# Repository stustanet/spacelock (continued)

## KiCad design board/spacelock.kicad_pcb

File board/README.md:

# Board design

Printed circuit board with all the electrical components.

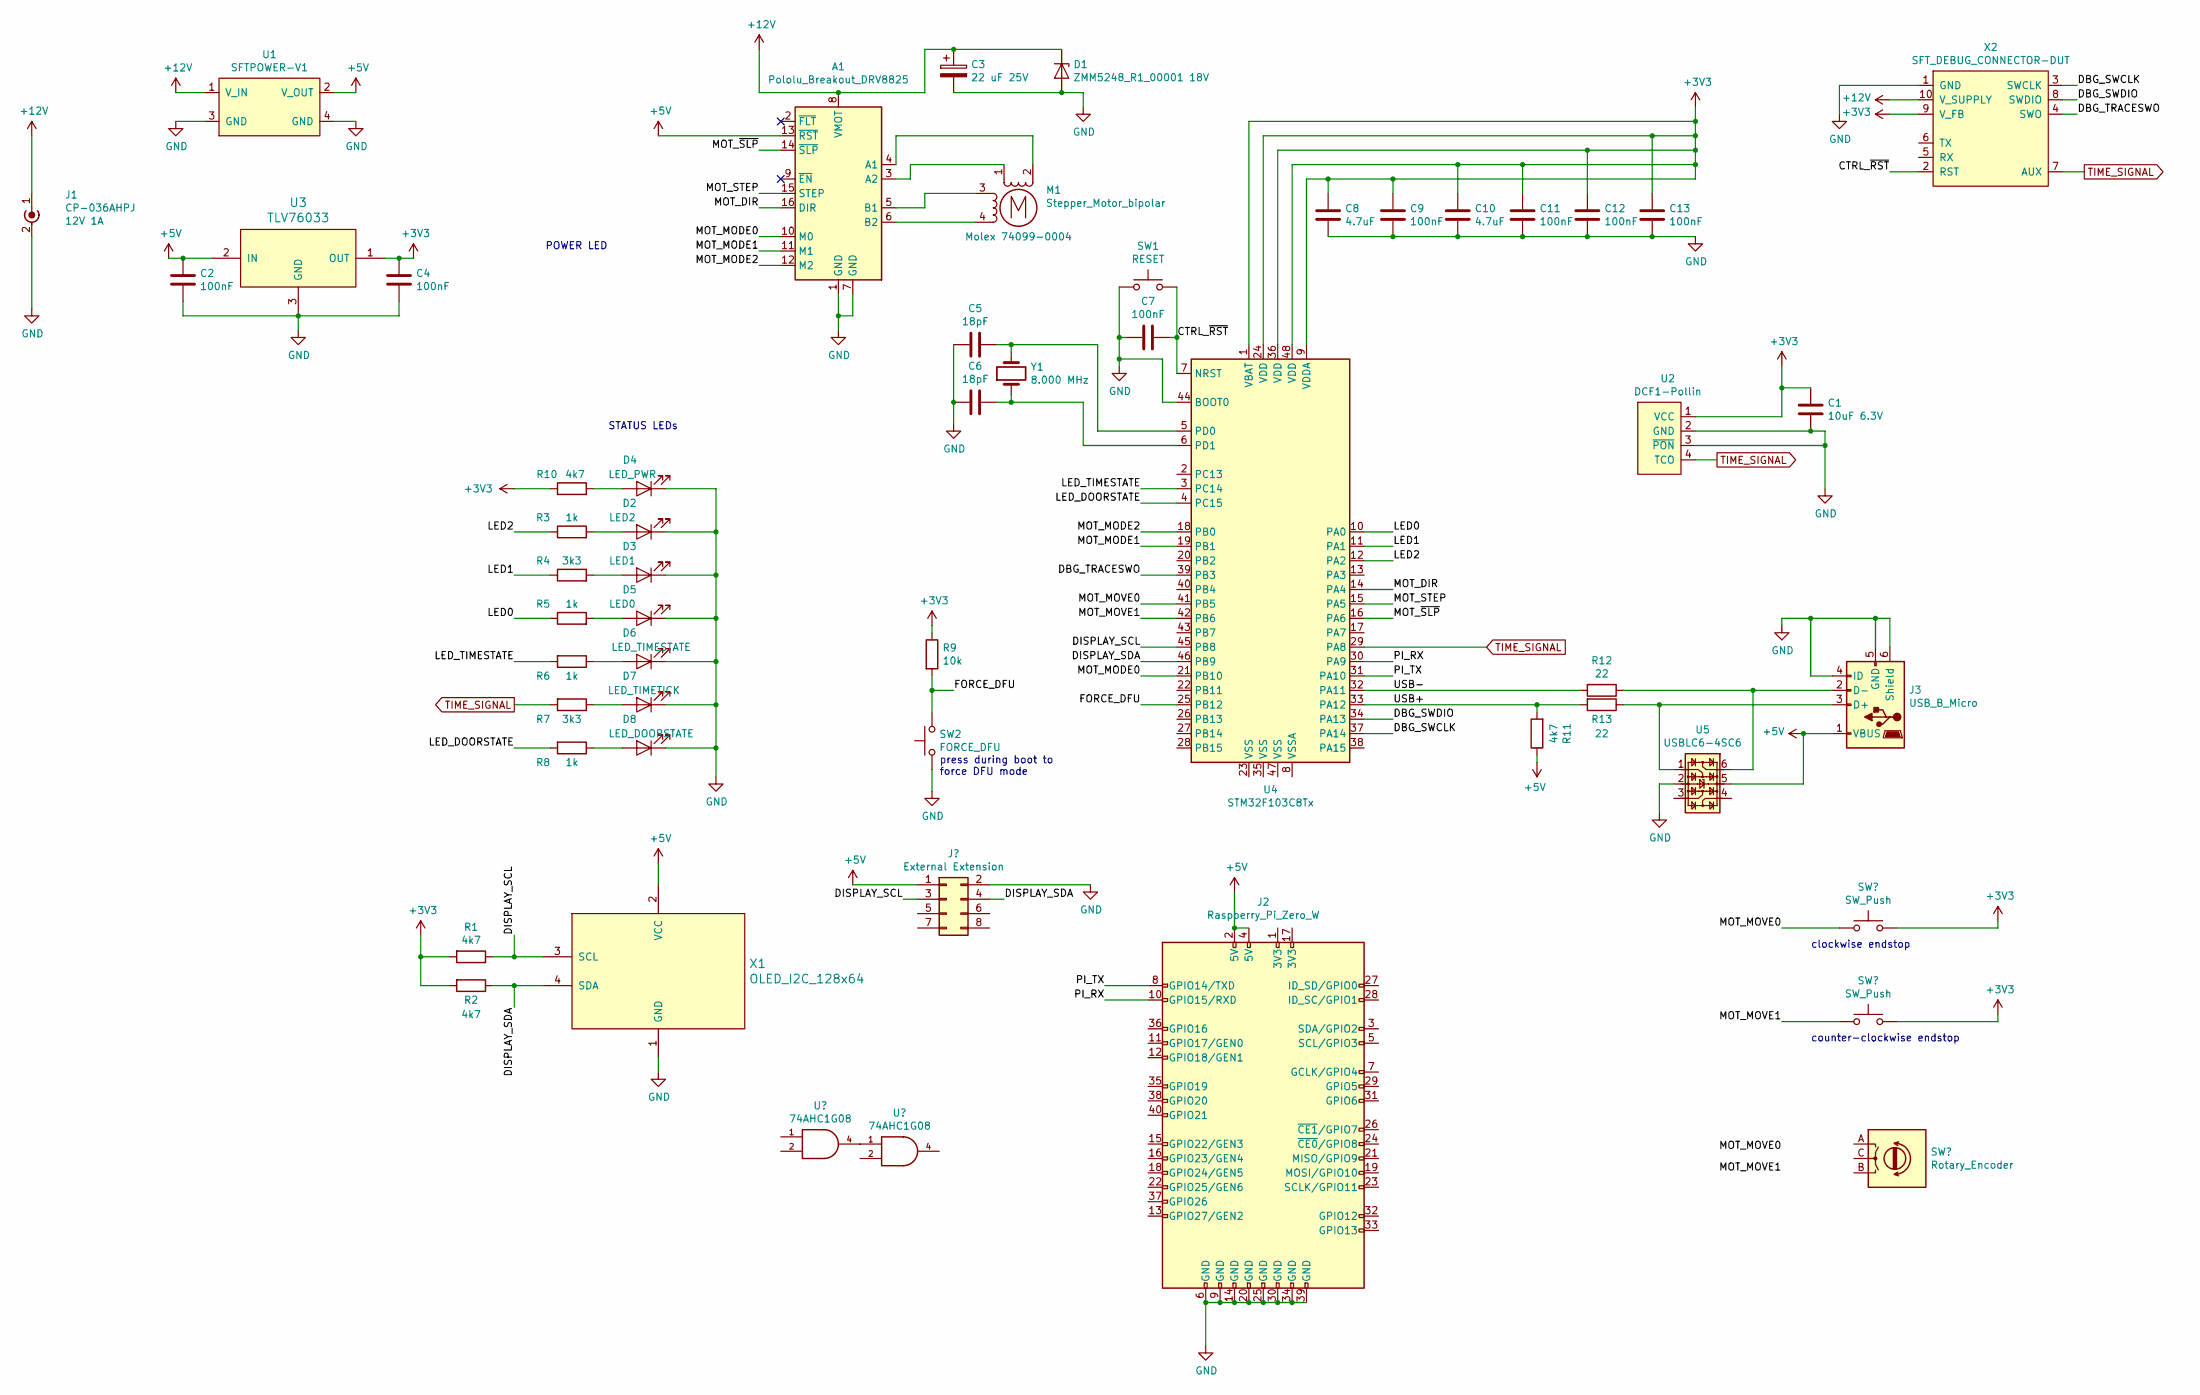
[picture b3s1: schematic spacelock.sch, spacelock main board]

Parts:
A1: Pololu_Breakout_DRV8825; Pololu_Breakout-16_15.2x20.3mm
C1: 10uF 6.3V; C_1206_3216Metric_Pad1.42x1.75mm_HandSolder
C2, C4, C7, C9, C11, C12, C13: 100nF; C_0603_1608Metric_Pad1.05x0.95mm_HandSolder
C3: 22 uF 25V; C_1206_3216Metric_Pad1.42x1.75mm_HandSolder
C5, C6: 18pF; C_0603_1608Metric_Pad1.05x0.95mm_HandSolder; MPN generic C0603
C8, C10: 4.7uF; C_0603_1608Metric_Pad1.05x0.95mm_HandSolder
D1: ZMM5248_R1_00001 18V; D_MiniMELF_Handsoldering; MPN ZMM5248B
D2: LED2; LED_0805_2012Metric_Pad1.15x1.40mm_HandSolder
D3: LED1; LED_0805_2012Metric_Pad1.15x1.40mm_HandSolder
D4: LED_PWR; LED_0805_2012Metric_Pad1.15x1.40mm_HandSolder
D5: LED0; LED_0805_2012Metric_Pad1.15x1.40mm_HandSolder
D6: LED_TIMESTATE; LED_0805_2012Metric_Pad1.15x1.40mm_HandSolder
D7: LED_TIMETICK; LED_0805_2012Metric_Pad1.15x1.40mm_HandSolder
D8: LED_DOORSTATE; LED_0805_2012Metric_Pad1.15x1.40mm_HandSolder
J1: CP-036AHPJ; BarrelJack_CUI_PJ-063AH_Horizontal
J2: Raspberry_Pi_Zero_W; Raspberry_Pi_Zero_Socketed_THT_FaceDown_MountingHoles
J3: USB_B_Micro; Amphenol_10118194; MPN Amphenol 10118194-0001LF
M1: Stepper_Motor_bipolar; PinHeader_1x04_P2.54mm_Horizontal; MPN Molex 74099-0004
R1, R2, R10: 4k7; R_0603_1608Metric_Pad1.05x0.95mm_HandSolder; MPN generic R0603
R3, R5, R6, R8: 1k; R_0603_1608Metric_Pad1.05x0.95mm_HandSolder
R4, R7: 3k3; R_0603_1608Metric_Pad1.05x0.95mm_HandSolder
R9: 10k; R_0603_1608Metric_Pad1.05x0.95mm_HandSolder
R11: 4k7; R_0603_1608Metric_Pad1.05x0.95mm_HandSolder
R12, R13: 22; R_0603_1608Metric_Pad1.05x0.95mm_HandSolder; MPN generic R0603
SW1: RESET; SW_PUSH_6mm_H4.3mm; MPN PANASONIC EVQPAE05R
SW2: FORCE_DFU; SW_PUSH_6mm_H4.3mm; MPN PANASONIC EVQPAE05R
U1: SFTPOWER-V1; SFTPOWERv1
U2: DCF1-Pollin
U3: TLV76033; SOT-23
U4: STM32F103C8Tx; LQFP-48_7x7mm_P0.5mm
U5: USBLC6-4SC6; SOT-23-6
X1: OLED_I2C_128x64; OLED_128x64_096in_IZOKEE
X2: SFT_DEBUG_CONNECTOR-DUT; Tag-Connect_TC2050-IDC-FP_2x05_P1.27mm_Vertical
Y1: 8.000 MHz; Crystal_HC49-U_Vertical; MPN ZheJiang B08000J065

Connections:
+3V3: C1.1, C4.1, C8.1, C9.1, C10.1, C11.1, C12.1, C13.1, R1.2, R2.2, R9.1, R10.1, U2.1 (VCC), U3.1 (OUT), U4.1 (VBAT), U4.9 (VDDA), U4.24 (VDD), U4.36 (VDD), U4.48 (VDD), X2.9 (V_FB)
/CTRL_~RST: C7.1, SW1.2, U4.7 (NRST), X2.2 (RST)
/DBG_SWCLK: U4.37 (PA14), X2.3 (SWCLK)
/DBG_SWDIO: U4.34 (PA13), X2.8 (SWDIO)
/DBG_TRACESWO: U4.39 (PB3), X2.4 (SWO)
/DISPLAY_SCL: R1.1, U4.45 (PB8), X1.3 (SCL)
/DISPLAY_SDA: R2.1, U4.46 (PB9), X1.4 (SDA)
/END_CCLKWSE: U4.42 (PB6)
/END_CLKWSE: U4.41 (PB5)
/FORCE_DFU: R9.2, SW2.2, U4.25 (PB12)
/LED0: R5.1, U4.10 (PA0)
/LED1: R4.1, U4.11 (PA1)
/LED2: R3.1, U4.12 (PA2)
/LED_DOORSTATE: R8.2, U4.4 (PC15)
/LED_TIMESTATE: R6.2, U4.3 (PC14)
/MOT_DIR: A1.16 (DIR), U4.14 (PA4)
/MOT_MODE0: A1.10 (M0), U4.21 (PB10)
/MOT_MODE1: A1.11 (M1), U4.19 (PB1)
/MOT_MODE2: A1.12 (M2), U4.18 (PB0)
/MOT_STEP: A1.15 (STEP), U4.15 (PA5)
/MOT_~SLP: A1.14 (~SLP), U4.16 (PA6)
/PI_RX: J2.10 (GPIO15/RXD), U4.30 (PA9)
/PI_TX: J2.8 (GPIO14/TXD), U4.31 (PA10)
/USB+: R11.2, R13.2, U4.33 (PA12)
/USB-: R12.2, U4.32 (PA11)
GND: A1.1 (GND), A1.7 (GND), C1.2, C2.2, C3.2, C4.2, C5.2, C6.2, C7.2, C8.2, C9.2, C10.2, C11.2, C12.2, C13.2, D1.2 (A), D2.1 (K), D3.1 (K), D4.1 (K), D5.1 (K), D6.1 (K), D7.1 (K), D8.1 (K), J1.2 (Ext), J2.6 (GND), J2.9 (GND), J2.14 (GND), J2.20 (GND), J2.25 (GND), J2.30 (GND), J2.34 (GND), J2.39 (GND), J3.4 (ID), J3.5 (GND), J3.6 (Shield), SW1.1, SW2.1, U1.3 (GND), U1.4 (GND), U2.2 (GND), U2.3 (~PON), U3.3 (GND), U4.44 (BOOT0), U5.2, X1.1 (GND), X2.1 (GND)
unnamed: A1.3 (A2), M1.1
unnamed: A1.4 (A1), M1.2 (-)
unnamed: A1.5 (B1), M1.3
unnamed: A1.6 (B2), M1.4
unnamed: C5.1, U4.5 (PD0), Y1.2
unnamed: C6.1, U4.6 (PD1), Y1.1
unnamed: D2.2 (A), R3.2
unnamed: D3.2 (A), R4.2
unnamed: D4.2 (A), R10.2
unnamed: D5.2 (A), R5.2
unnamed: D6.2 (A), R6.1
unnamed: D7.2 (A), R7.1
unnamed: D8.2 (A), R8.1
unnamed: J3.2 (D-), R12.1, U5.6
unnamed: J3.3 (D+), R13.1, U5.1

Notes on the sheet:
press during boot to force DFU mode
POWER LED
STATUS LEDs
counter-clockwise endstop
clockwise endstop

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
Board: 2 copper layers, 49 parts (0 on the bottom side), 42 nets, no tracks yet.

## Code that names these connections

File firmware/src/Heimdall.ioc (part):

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Mcu.Name=STM32F103C(8-B)Tx
Mcu.Package=LQFP48
Mcu.UserName=STM32F103C8Tx
PA1.Signal=GPIO_Input
PA10.Mode=Asynchronous
PA10.Signal=USART1_RX
PA13.Mode=Serial_Wire
PA13.Signal=SYS_JTMS-SWDIO
PA14.Mode=Serial_Wire
PA14.Signal=SYS_JTCK-SWCLK
PA2.Signal=GPIO_Output
PA3.Signal=GPIO_Output
PA4.Signal=GPIO_Output
PA5.Signal=GPIO_Output
PA6.Signal=GPIO_Output
PA7.Signal=GPIO_Output
PA9.Mode=Asynchronous
PA9.Signal=USART1_TX
PD0-OSC_IN.Mode=HSE-External-Oscillator
PD0-OSC_IN.Signal=RCC_OSC_IN
PD1-OSC_OUT.Mode=HSE-External-Oscillator
PD1-OSC_OUT.Signal=RCC_OSC_OUT
RCC.SYSCLKFreq_VALUE=72000000
RCC.SYSCLKSource=RCC_SYSCLKSOURCE_PLLCLK
board=custom

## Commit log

2019-05-07 lololo für jj <3
2019-05-07 danke wolfi
2019-05-08 loltest
2019-05-16 add gregorian calendar
2019-05-20 add dcf77, tests ok
2019-05-22 debug dcf77
2019-06-09 add hmac api
2019-06-09 implement hmac
2019-06-09 implement leds
2019-06-09 test hmac
2019-06-09 ignore test binaries
2019-06-09 add readme lol
2019-06-09 add more test binaries to gitignore
2019-06-09 ignore binaries
2019-06-09 add board and mount directories
2019-06-09 add database code
2019-06-10 Fix secret key
2019-06-21 some new web stuff
2019-06-22 select token validity by access configuration
2019-06-23 add qr code to web interface
2019-06-24 working bluetooth
2019-06-24 Change baudrate
2019-06-24 fix working bluetooth to make it more working
2019-06-24 bluetooth server
2019-06-24 beautify jf code
2019-07-05 add .vscode ignore
2019-07-05 add qrcode server and hardware interface
2019-07-05 fix ml mistakes
2019-07-05 add shebang
2019-07-09 [web] WIP management interface
2019-07-09 [web] session management for management
2019-07-11 database: add user and password management
2019-07-11 database: require username for various actions
2019-07-12 [web] WIP adapt to new database
2019-07-12 database: remove user names, use request ids instead
2019-07-12 database: fix returned table of user_list
2019-07-12 database: import pgcrypto module first
2019-07-12 database: function access rights recommendations
2019-07-14 [web] user management basically done
2019-07-14 [web] add req_id link functionality
2019-07-14 adjust dcf77 tolerances
2019-07-14 [web, db] fix sign_message, hopefully fix mobile web stuff
2019-07-14 [web] fix bluetooth js
2019-07-14 [web] make qr code nice again
2019-07-14 [web] open wifi link in new tab
2019-07-16 [web] fix database management, fix timezone issues
2019-07-16 nothing to see here, especially now
2019-07-16 add beeper to firmware
2019-07-23 [web] fix ui
2019-10-12 add redirect on csrf failure
2019-11-17 initial schematic stuff for board
2019-11-27 database: secret key updating support
    other notable changes:
    * `secret` is now initialized with a 32 0-byte key
    * `permissions` has a new colum called `hidden` which defaults to `false`
    * new functions for key updating:
    * keys are generated by sha256(random data + previous key)
    * the random data is transmitted to door firmware,
2019-11-28 database: fix null comparisons in `user_mod`
2019-12-03 database: fix for removed signer id column
2019-12-04 database: fix user_mod to change a null-name
2019-12-04 implement new db funcs, signing key update gui foo
2020-09-06 board: main connectivity
2020-11-20 make bluetoothserver executable
2020-11-20 add serial server
2021-01-11 Add base64 decoder helper
2021-01-11 Update board
2021-03-19 Bump pillow from 7.2.0 to 8.1.1 in /web
    Bumps [pillow](https://github.com/python-pillow/Pillow) from 7.2.0 to 8.1.1.
    - [Release notes](https://github.com/python-pillow/Pillow/releases)
    - [Changelog](https://github.com/python-pillow/Pillow/blob/master/CHANGES.rst)
    - [Commits](https://github.com/python-pillow/Pillow/compare/7.2.0...8.1.1)
2021-03-20 Bump jinja2 from 2.11.2 to 2.11.3 in /web
    Bumps [jinja2](https://github.com/pallets/jinja) from 2.11.2 to 2.11.3.
    - [Release notes](https://github.com/pallets/jinja/releases)
    - [Changelog](https://github.com/pallets/jinja/blob/master/CHANGES.rst)
    - [Commits](https://github.com/pallets/jinja/compare/2.11.2...2.11.3)
2021-03-30 Add A2HS support
    https://developer.mozilla.org/en-US/docs/Web/Progressive_web_apps/Add_to_home_screen
2021-03-30 Fix invalid manifest file
2021-06-08 Bump pillow from 7.2.0 to 8.2.0 in /web
    Bumps [pillow](https://github.com/python-pillow/Pillow) from 7.2.0 to 8.2.0.
    - [Release notes](https://github.com/python-pillow/Pillow/releases)
    - [Changelog](https://github.com/python-pillow/Pillow/blob/master/CHANGES.rst)
    - [Commits](https://github.com/python-pillow/Pillow/compare/7.2.0...8.2.0)
    ---
    updated-dependencies:
2021-08-06 Show, if an user's access is expired.
2021-09-08 Bump pillow from 7.2.0 to 8.3.2 in /web
    Bumps [pillow](https://github.com/python-pillow/Pillow) from 7.2.0 to 8.3.2.
    - [Release notes](https://github.com/python-pillow/Pillow/releases)
    - [Changelog](https://github.com/python-pillow/Pillow/blob/master/CHANGES.rst)
    - [Commits](https://github.com/python-pillow/Pillow/compare/7.2.0...8.3.2)
    ---
    updated-dependencies:
2022-01-13 Bump pillow from 7.2.0 to 9.0.0 in /web
    Bumps [pillow](https://github.com/python-pillow/Pillow) from 7.2.0 to 9.0.0.
    - [Release notes](https://github.com/python-pillow/Pillow/releases)
    - [Changelog](https://github.com/python-pillow/Pillow/blob/main/CHANGES.rst)
    - [Commits](https://github.com/python-pillow/Pillow/compare/7.2.0...9.0.0)
    ---
    updated-dependencies:
2022-03-12 Bump pillow from 7.2.0 to 9.0.1 in /web
    Bumps [pillow](https://github.com/python-pillow/Pillow) from 7.2.0 to 9.0.1.
    - [Release notes](https://github.com/python-pillow/Pillow/releases)
    - [Changelog](https://github.com/python-pillow/Pillow/blob/main/CHANGES.rst)
    - [Commits](https://github.com/python-pillow/Pillow/compare/7.2.0...9.0.1)
    ---
    updated-dependencies:
2022-04-03 Notify the user when its access will expire
2022-04-03 Add reload button to generate a new code
2022-04-05 Updating all requirements to their newest version
2022-12-18 add border around qrcode
2022-12-18 flush after printing postgres error
2022-12-18 set title to spacelock
2022-12-18 bind csrf token lifetime to session
2023-04-30 web: show token validity
2023-06-20 Port board files to kicad v6
2023-06-20 feat: parser for uart data to csv
2023-06-20 feat: sample adc and write out on uart
2023-06-20 feat: Current-based end-stop detection
2023-06-20 Port firmware to board_v1
2023-06-20 fix: Adapt parameters for actual door
2023-06-20 fix: correct serial baud rate for logging script
2023-06-20 Fix board schematic and documentation after initial commissioning
2023-06-20 Add reset_secret_key() function for use from gdb
2023-06-20 fix: type for time information
2023-06-20 process_data.py: Improved debug prints for connection setup
2023-06-20 Disable backdoor and key reset-on-reset
2023-06-20 Add config.h for parametrization
2023-06-21 refactor: add defines and remove constants from cpp files
2023-06-21 feat: enable and disable components, add door sensor support and Biederstein Config
2023-07-11 feat: more readme and cleaner config
2024-01-21 inner board v1.1, rtc, QR-connector
2024-01-21 board v1.1: clean up, create own folder
2024-02-05 add door mounting cad model
2024-03-02 aktueller stand
2024-03-09 new protocol, init msg
2024-03-09 stand heute, noch nicht im geringsten getestet
2024-03-10 update msg
2024-03-10 weiter entwickelt
2024-03-10 use libnacl
2024-03-10 flush msg
2024-03-10 weiter rummachen
2024-03-16 weiter rummachen: debuggen
2024-03-20 write keys to flash
2024-03-24 stand nach 2 hopfenweise
2024-03-25 stand nach am tag nach den 2 hopfenweisen
2024-03-25 testdaten
2024-03-30 cleanup valid_from / valid_to and intervals
2024-03-31 sign_message: do not change validation time
2024-03-31 decode.py
2024-03-31 add tests/example-data/message01.csv
    contains verify-key message pairs
2024-03-31 more changes
2024-04-01 more views
2024-04-01 only create init message for a door if system is owner
2024-04-07 debug stuff
2024-04-21 RTC integration
2024-04-27 AB keystorage
2024-04-27 reorganise setup file; implement automatic ALL keyrings
2024-04-28 timebased housekeeping
2024-04-28 weitere funktionen;
    database/setup_1051_code.sql ist nicht in benutzbaren zustand
2024-06-29 weiter bauen
    database/setup_1051_code.sql geht nun, zumindest compat_gen_token
2024-09-01 better RTC readout
2024-09-05 fix flush cmd
2024-12-12 database: document correct order of sql files for setup
2024-12-15 web: get frontend to run
2024-12-15 correct sequence of initialisation
